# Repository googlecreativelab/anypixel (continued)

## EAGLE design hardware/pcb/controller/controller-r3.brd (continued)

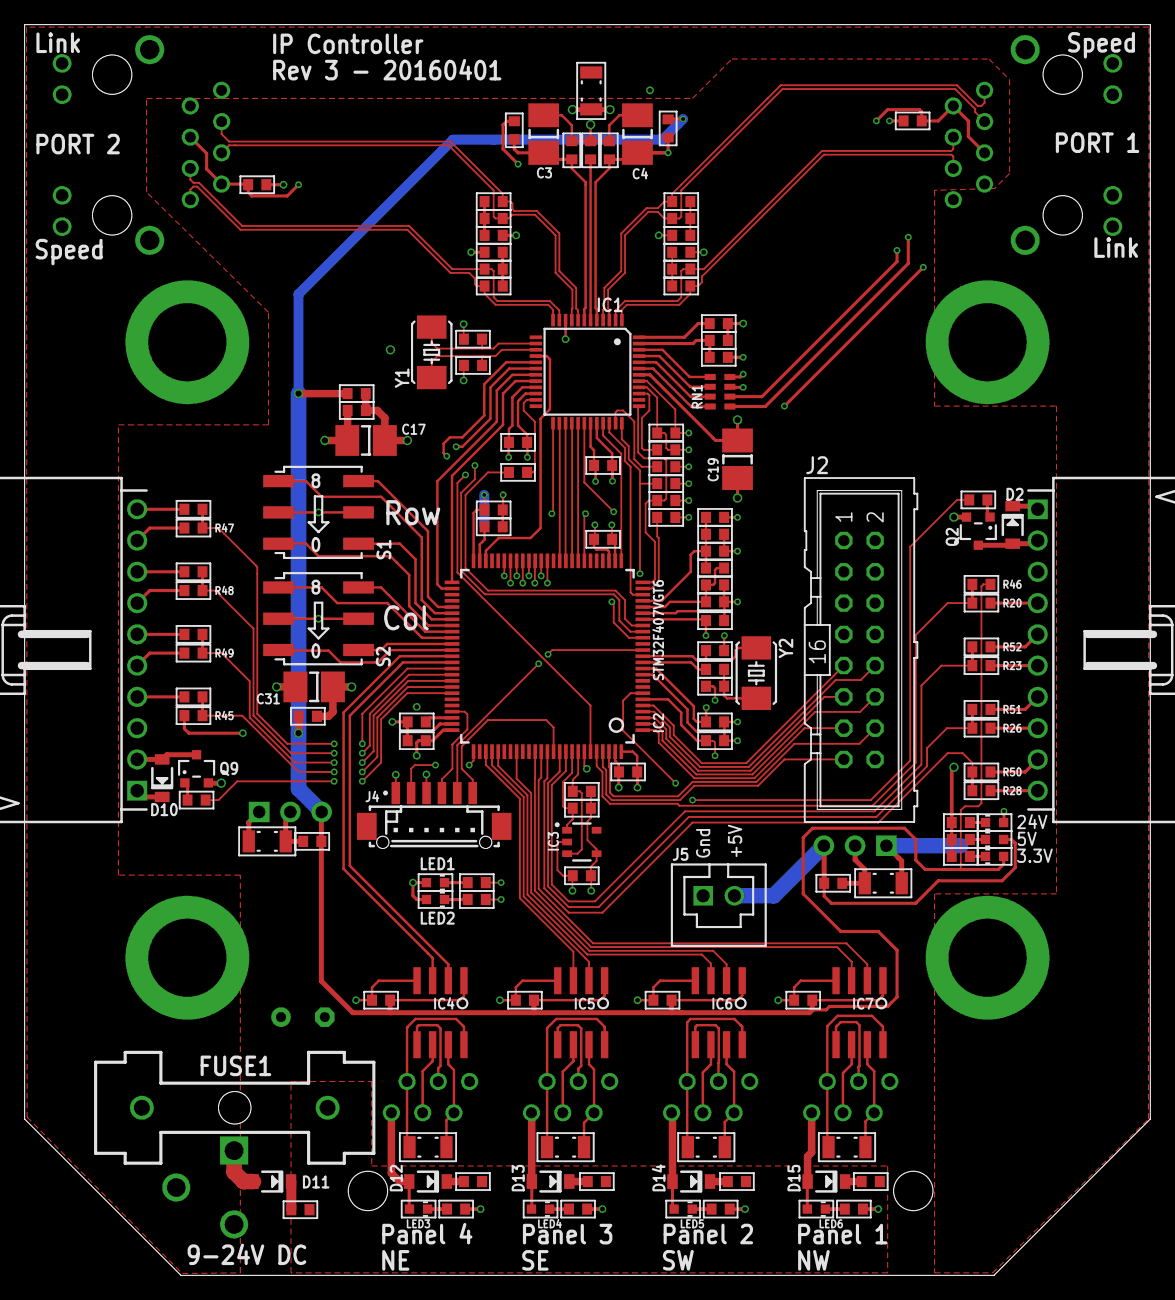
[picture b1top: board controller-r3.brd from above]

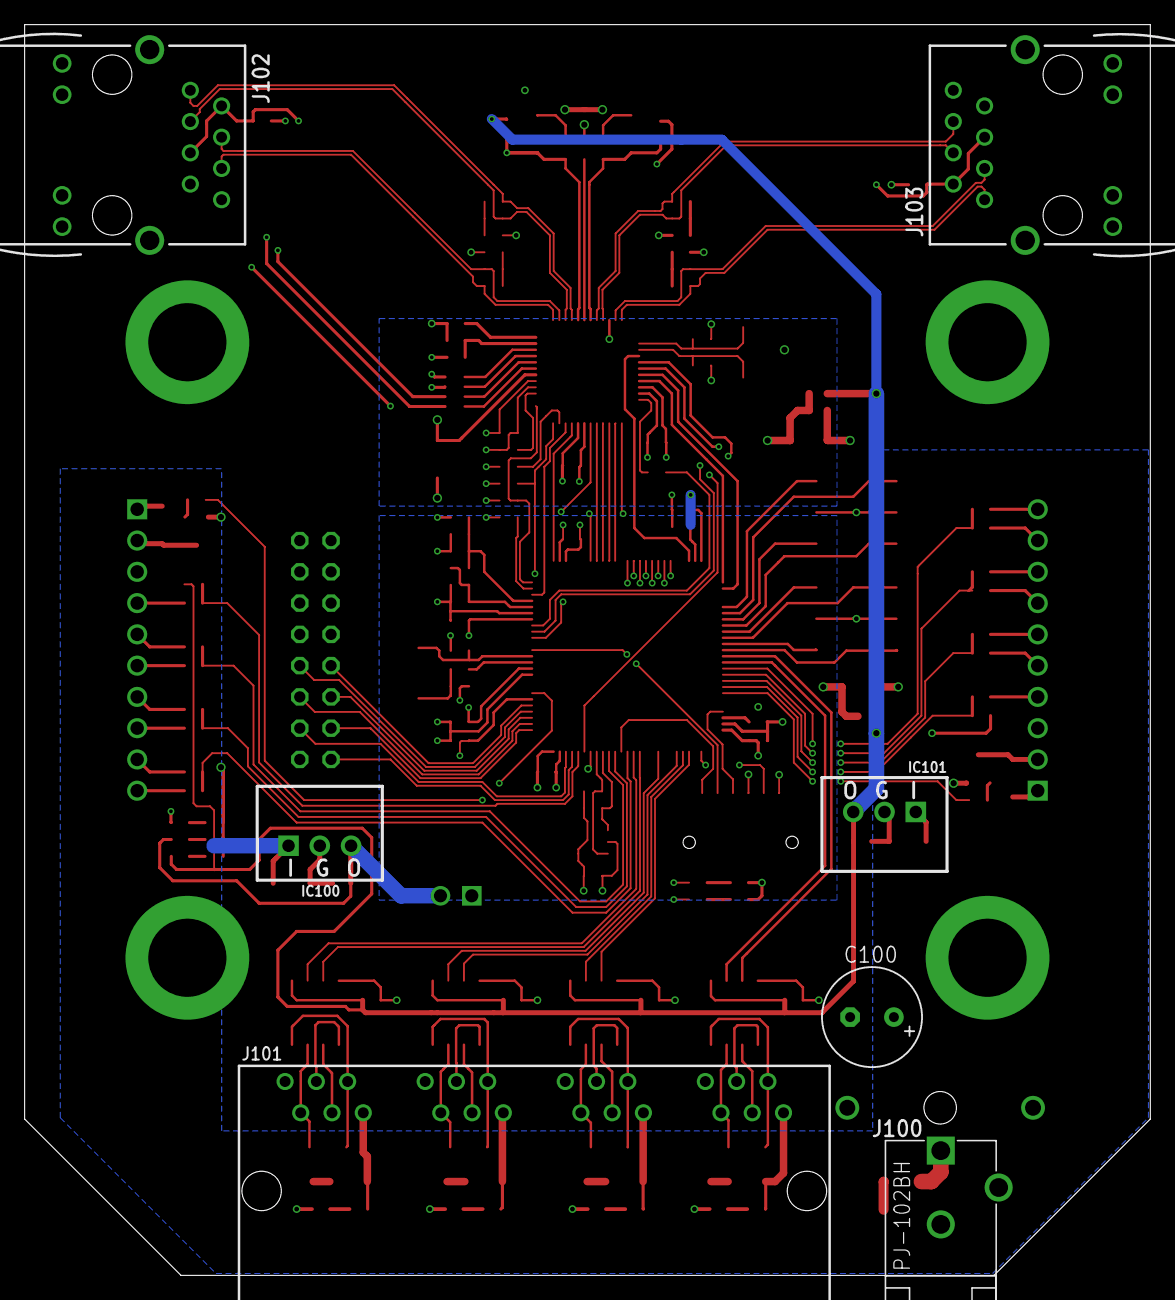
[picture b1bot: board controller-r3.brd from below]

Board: 4 copper layers, 91.4 x 101.6 mm, 154 parts (7 on the bottom side), 157 nets.

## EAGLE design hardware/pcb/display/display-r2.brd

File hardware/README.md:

## Hardware

- **/mechanical** - CAD files, engineering drawings, and assembly diagrams for the buttonwall installation in NYC.
- **/pcb** - EAGLE files and PDFs for 7x7 LED grid and network controller board.
- **/wiring** - Wiring harness and power diagrams for buttonwall installation in NYC.

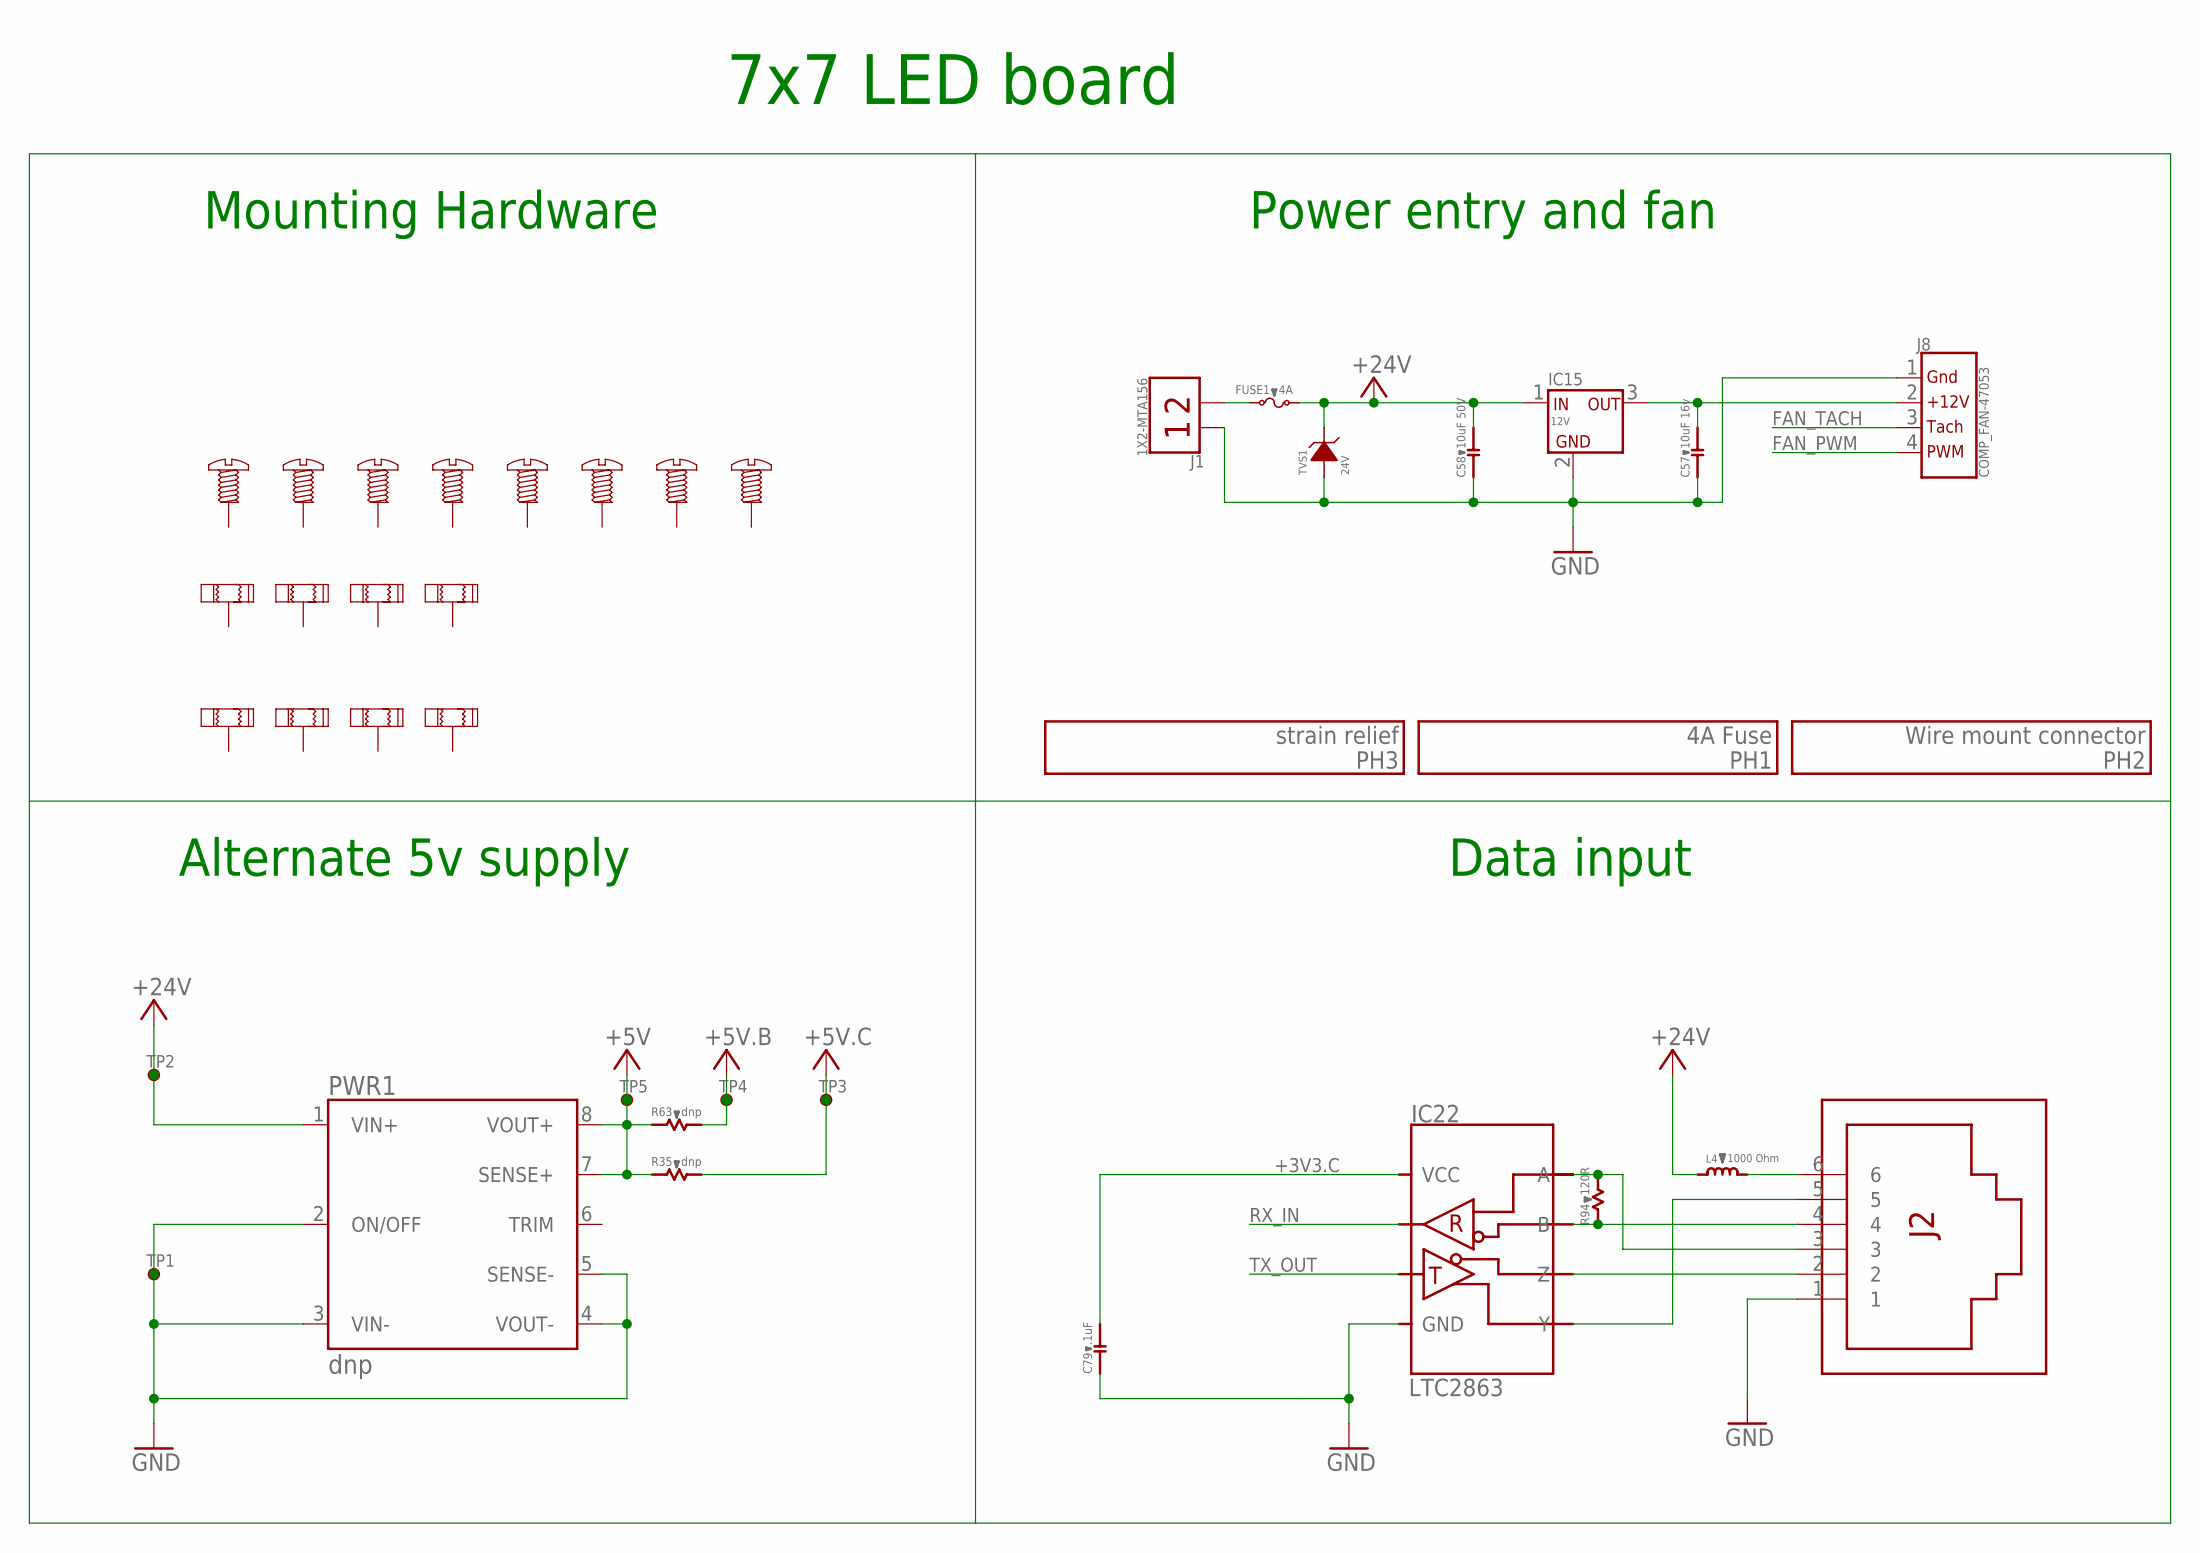
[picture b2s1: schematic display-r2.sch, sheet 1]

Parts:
C57: 10uF 16v; C0805B; PARTNO CGA4J1X5R1C106K125AC
C58: 10uF 50V; C1206B; PARTNO CL31A106KBHNNNE
C79: .1uF; C0603B; PARTNO CGA3E2X7R1H104K080AA
FUSE1: 4A; 649; PARTNO 64900001039
IC15: 12V; P7805; PARTNO P7805-Q24-S12-S
IC22: LTC2863; SO08; PARTNO LTC2863IS8-1#PBF
J1: 1X2-MTA156; 640445-2; PARTNO 640445-2
J2: RJ12-JACK-RJE01; RJE01-660-01; PARTNO RJE0166001
J8: COMP_FAN-47053; 47053; PARTNO 0470531000
L4: 1000 Ohm; R0603B; PARTNO MMZ1608R102A
NUT1, NUT2, NUT3, NUT4: NUTSMTSO-632; SMTSO-632-2ET
NUT5, NUT6, NUT7, NUT8: NUTSMTSO-832; SMTSO-832-2ET
PWR1: dnp; PWR-1/4-BRICK
R35, R63: dnp; R0805B
R94: 120R; R1206B; PARTNO CRCW1206120RFKEA
SCREW1, SCREW2, SCREW3, SCREW4, SCREW5, SCREW6, SCREW7, SCREW8: SCREW-632-0-PSHP; SMTPR-6-1
TP1, TP2, TP3, TP4, TP5: TP-CIR30; SMD_CIR30
TVS1: 24V; SMC/DO214AB; PARTNO 4.0SMDJ24A

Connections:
+3V3.C: C79.2, IC22.1 (VCC); also elsewhere on the board
+5V: PWR1.7 (SENSE+), PWR1.8 (VOUT+), R35.1, R63.1, TP5.P$1; also elsewhere on the board
+5VB: R63.2, TP4.P$1; also elsewhere on the board
+5VC: R35.2, TP3.P$1; also elsewhere on the board
+24V: C58.2, FUSE1.2, IC15.1 (IN), L4.1, PWR1.1 (VIN+), TP2.P$1, TVS1.C (CATHODE); also elsewhere on the board
+24V_OUT: J2.6, L4.2
FAN_PWM: J8.4; also elsewhere on the board
FAN_TACH: J8.3; also elsewhere on the board
GND: C57.1, C58.1, C79.1, IC15.2 (GND), IC22.4 (GND), J1.1, J2.1, J8.1, PWR1.2 (ON/OFF), PWR1.3 (VIN-), PWR1.4 (VOUT-), PWR1.5 (SENSE-), TP1.P$1, TVS1.A (ANODE); also elsewhere on the board
unnamed: FUSE1.1, J1.2
unnamed: IC22.7 (B), J2.4, R94.1
unnamed: IC22.8 (A), J2.3, R94.2
unnamed: IC22.6 (Z), J2.2
unnamed: IC22.5 (Y), J2.5
OUT: C57.2, IC15.3 (OUT), J8.2
RX_IN: IC22.2 (RO); also elsewhere on the board
TX_OUT: IC22.3 (DI); also elsewhere on the board

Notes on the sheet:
Mounting Hardware
Power entry and fan
Alternate 5v supply
Data input
7x7 LED board

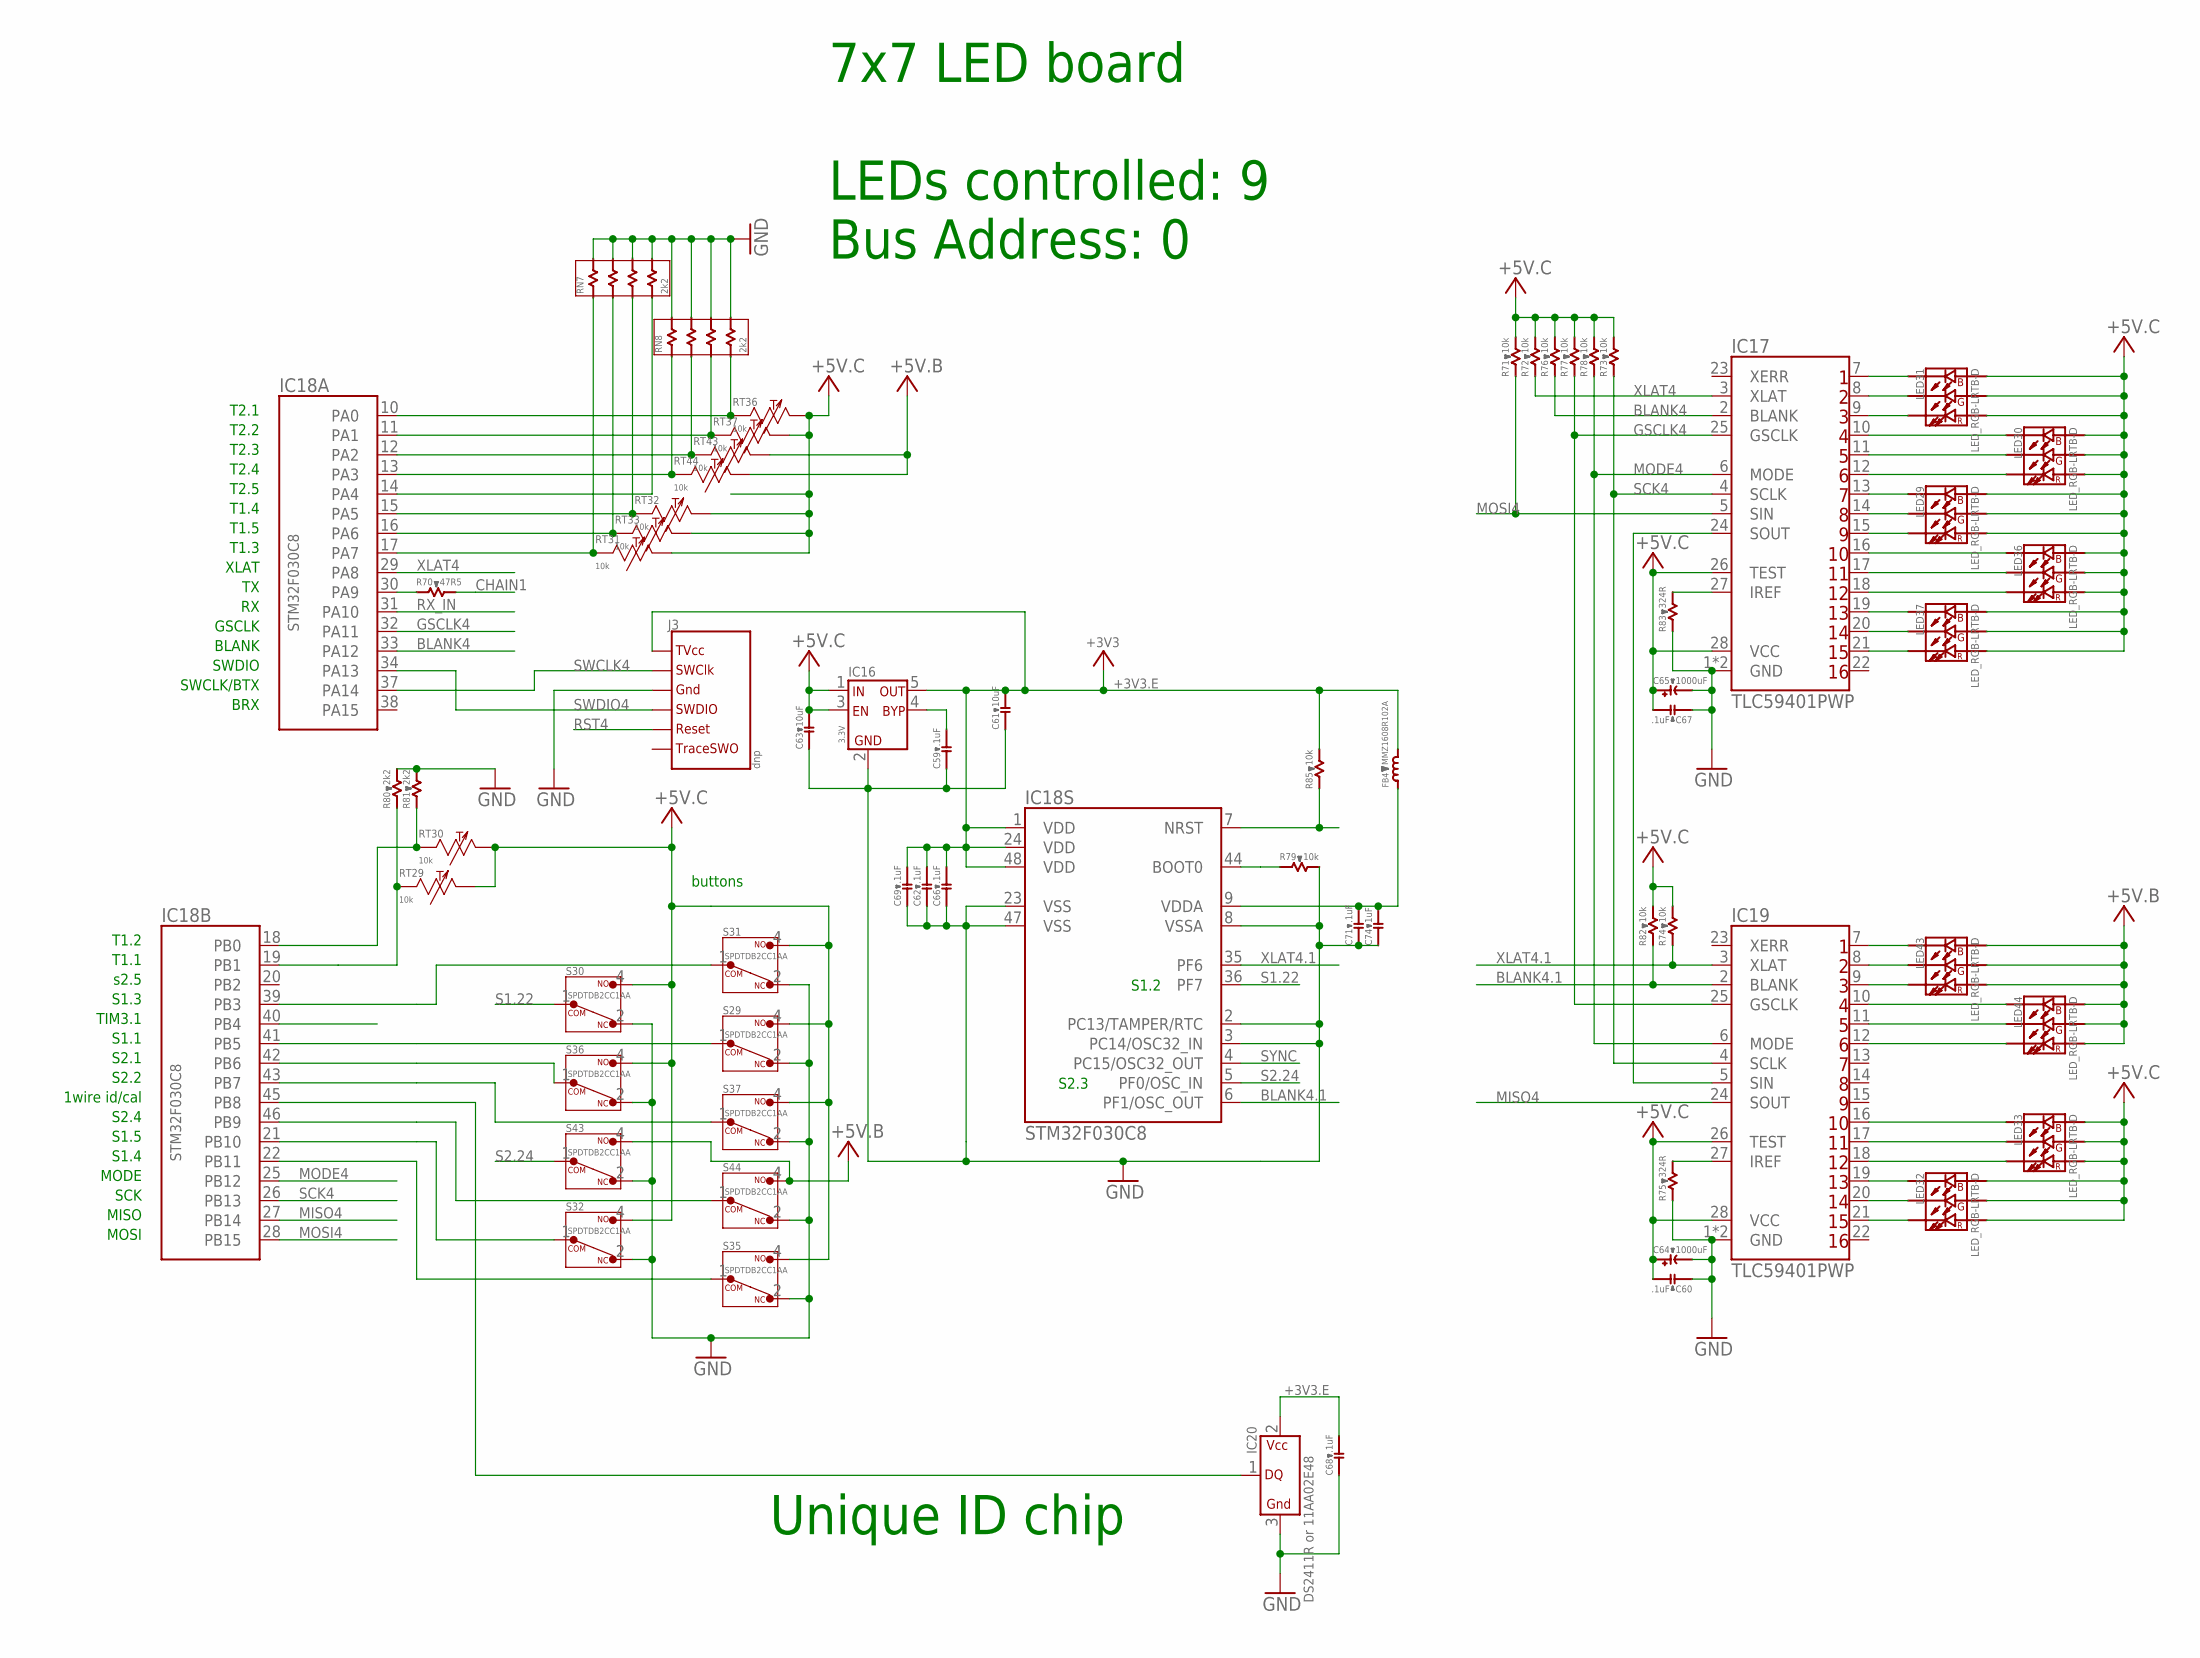
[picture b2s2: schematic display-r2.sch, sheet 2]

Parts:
C59, C60, C62, C66, C67, C68, C69, C71: .1uF; C0603B; PARTNO CGA3E2X7R1H104K080AA
C61, C63: 10uF; C0603B; PARTNO C1608X6S1A106M080AC
C64, C65: 1000uF; E5-10,5; PARTNO EKZN160ELL102MJ16S
C74: 1uF; C0603B; PARTNO CGA3E3X5R1H105K080AB
FB4: MMZ1608R102A; R0603B; PARTNO MMZ1608R102A
IC16: 3.3V; SOT-23-5; PARTNO TC2185-3.3VCTTR
IC17, IC19: TLC59401PWP; TSSOP28_PAD; PARTNO TLC59401PWPR
IC18: STM32F030C8; LQFP-48; PARTNO STM32F030C8T6
IC20: DS2411R or 11AA02E48; SOT-23; PARTNO 11AA02E48T-I/TT
J3: dnp; TC2030-IDC-NL
LED29, LED30, LED31, LED32, LED33, LED36, LED37, LED43, LED44: LED_RGB-LRTB-D; LRTB_C9TP-D; PARTNO LRTBC9TP-CWD5-1+D5E7-25+A
R70: 47R5; R0603B; PARTNO CRCW060347R5FKEA
R71, R72, R73, R74, R76, R77, R78, R79, R82, R85: 10k; R0603B; PARTNO CRCW060310K0FKEA
R75, R83: 324R; R0603B; PARTNO CRCW0603324RFKEA
R80, R81: 2k2; R0603B; PARTNO CRCW06032K20FKEA
RN7, RN8: 2k2; CAY16; PARTNO CAY16-2201F4LF
RT29, RT30, RT31, RT32, RT33, RT36, RT37, RT43, RT44: 10k; R0603Y; PARTNO NCP18XH103F03RB
S29, S30, S31, S32, S35, S36, S37, S43, S44: SPDTDB2CC1AA; DB2CC1AA; PARTNO DB2CC1AA

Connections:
+3V3.E: C61.2, C62.2, C66.2, C68.2, C69.2, FB4.2, IC16.5 (OUT), IC18.1 (VDD), IC18.24 (VDD), IC18.48 (VDD), IC20.2 (VCC), J3.1 (TVCC), R85.2
+5VB: LED43.A1 (ANODE_R), LED43.A2 (ANODE_G), LED43.A3 (ANODE_B), LED44.A1 (ANODE_R), LED44.A2 (ANODE_G), LED44.A3 (ANODE_B), RT43.2, RT44.2, S43.4 (NO), S44.4 (NO); also elsewhere on the board
+5VC: C60.2, C63.2, C64.+, C65.+, C67.2, IC16.1 (IN), IC16.3 (EN), IC17.26 (TEST), IC17.28 (VCC), IC19.26 (TEST), IC19.28 (VCC), LED29.A1 (ANODE_R), LED29.A2 (ANODE_G), LED29.A3 (ANODE_B), LED30.A1 (ANODE_R), LED30.A2 (ANODE_G), LED30.A3 (ANODE_B), LED31.A1 (ANODE_R), LED31.A2 (ANODE_G), LED31.A3 (ANODE_B), LED32.A1 (ANODE_R), LED32.A2 (ANODE_G), LED32.A3 (ANODE_B), LED33.A1 (ANODE_R), LED33.A2 (ANODE_G), LED33.A3 (ANODE_B), LED36.A1 (ANODE_R), LED36.A2 (ANODE_G), LED36.A3 (ANODE_B), LED37.A1 (ANODE_R), LED37.A2 (ANODE_G), LED37.A3 (ANODE_B), R71.2, R72.2, R73.2, R74.2, R76.2, R77.2, R78.2, R82.2, RT29.2, RT30.2, RT31.2, RT32.2, RT33.2, RT36.2, RT37.2, S29.4 (NO), S30.4 (NO), S31.4 (NO), S32.4 (NO), S35.4 (NO), S36.4 (NO), S37.4 (NO); also elsewhere on the board
BLANK4: IC17.2 (BLANK), IC18.33 (PA12), R76.1
BLANK4.1: IC18.6 (PF1/OSC_OUT), IC19.2 (BLANK), R82.1
CHAIN1: R70.2; also elsewhere on the board
GND: C59.1, C60.1, C61.1, C62.1, C63.1, C64.-, C65.-, C66.1, C67.1, C68.1, C69.1, C71.1, C74.1, IC16.2 (GND), IC17.1 (GND), IC17.PAD (GND), IC18.2 (PC13/TAMPER/RTC), IC18.3 (PC14/OSC32_IN), IC18.8 (VSSA), IC18.23 (VSS), IC18.47 (VSS), IC19.1 (GND), IC19.PAD (GND), IC20.3 (GND), J3.5 (GND), R75.1, R79.2, R80.2, R81.2, R83.1, RN7.A2, RN7.B2, RN7.C2, RN7.D2, RN8.A2, RN8.B2, RN8.C2, RN8.D2, S29.2 (NC), S30.2 (NC), S31.2 (NC), S32.2 (NC), S35.2 (NC), S36.2 (NC), S37.2 (NC), S43.2 (NC), S44.2 (NC); also elsewhere on the board
GSCLK4: IC17.25 (GSCLK), IC18.32 (PA11), IC19.25 (GSCLK), R77.1
MISO4: IC18.27 (PB14), IC19.24 (SOUT)
MODE4: IC17.6 (MODE), IC18.25 (PB12), IC19.6 (MODE), R78.1
MOSI4: IC17.5 (SIN), IC18.28 (PB15), R71.1
unnamed: IC18.44 (BOOT0), R79.1
unnamed: C71.2, C74.2, FB4.1, IC18.9 (VDDA)
unnamed: C59.2, IC16.4 (BYPASS)
unnamed: IC17.24 (SOUT), IC19.5 (SIN)
unnamed: IC19.27 (IREF), R75.2
unnamed: IC17.27 (IREF), R83.2
unnamed: IC17.7 (OUT1), LED31.C3 (CATHODE_B)
unnamed: IC17.8 (OUT2), LED31.C2 (CATHODE_G)
unnamed: IC17.9 (OUT3), LED31.C1 (CATHODE_R)
unnamed: IC17.10 (OUT4), LED30.C3 (CATHODE_B)
unnamed: IC17.11 (OUT5), LED30.C2 (CATHODE_G)
unnamed: IC17.12 (OUT6), LED30.C1 (CATHODE_R)
unnamed: IC17.13 (OUT7), LED29.C3 (CATHODE_B)
unnamed: IC17.14 (OUT8), LED29.C2 (CATHODE_G)
unnamed: IC17.15 (OUT9), LED29.C1 (CATHODE_R)
unnamed: IC17.16 (OUT10), LED36.C3 (CATHODE_B)
unnamed: IC17.17 (OUT11), LED36.C2 (CATHODE_G)
unnamed: IC17.18 (OUT12), LED36.C1 (CATHODE_R)
unnamed: IC17.19 (OUT13), LED37.C3 (CATHODE_B)
unnamed: IC17.20 (OUT14), LED37.C2 (CATHODE_G)
unnamed: IC17.21 (OUT15), LED37.C1 (CATHODE_R)
unnamed: IC19.7 (OUT1), LED43.C3 (CATHODE_B)
unnamed: IC19.8 (OUT2), LED43.C2 (CATHODE_G)
unnamed: IC19.9 (OUT3), LED43.C1 (CATHODE_R)
unnamed: IC19.10 (OUT4), LED44.C3 (CATHODE_B)
unnamed: IC19.11 (OUT5), LED44.C2 (CATHODE_G)
unnamed: IC19.12 (OUT6), LED44.C1 (CATHODE_R)
unnamed: IC19.16 (OUT10), LED33.C3 (CATHODE_B)
unnamed: IC19.17 (OUT11), LED33.C2 (CATHODE_G)
unnamed: IC19.18 (OUT12), LED33.C1 (CATHODE_R)
unnamed: IC19.19 (OUT13), LED32.C3 (CATHODE_B)
unnamed: IC19.20 (OUT14), LED32.C2 (CATHODE_G)
unnamed: IC19.21 (OUT15), LED32.C1 (CATHODE_R)
unnamed: IC18.30 (PA9), R70.1
RST4: IC18.7 (NRST), J3.3 (RESET), R85.1
RX_IN: IC18.31 (PA10); also elsewhere on the board
S1.21: IC18.39 (PB3), S31.1 (COM)
S1.22: IC18.36 (PF7), S30.1 (COM)
S1.23: IC18.41 (PB5), S29.1 (COM)
S1.24: IC18.21 (PB10), S32.1 (COM)
S1.25: IC18.22 (PB11), S35.1 (COM)
S2.22: IC18.42 (PB6), S36.1 (COM)
S2.23: IC18.43 (PB7), S37.1 (COM)
S2.24: IC18.5 (PF0/OSC_IN), S43.1 (COM)
S2.25: IC18.46 (PB9), S44.1 (COM)
SCK4: IC17.4 (SCLK), IC18.26 (PB13), IC19.4 (SCLK), R73.1
SWCLK4: IC18.37 (PA14), J3.4 (SWCLK)
SWDIO4: IC18.34 (PA13), J3.2 (SWDIO)
SYNC: IC18.4 (PC15/OSC32_OUT); also elsewhere on the board
T41: IC18.14 (PA4), RN7.D1
T42: IC18.15 (PA5), RN7.C1, RT32.1
T43: IC18.16 (PA6), RN7.B1, RT33.1
T44: IC18.17 (PA7), RN7.A1, RT31.1
T45: IC18.18 (PB0), R81.1, RT30.1
T46: IC18.19 (PB1), R80.1, RT29.1
T47: IC18.13 (PA3), RN8.A1, RT44.1
T48: IC18.12 (PA2), RN8.B1, RT43.1
T49: IC18.11 (PA1), RN8.C1, RT37.1
T50: IC18.10 (PA0), RN8.D1, RT36.1
TIM3.5: IC18.40 (PB4)
TIM16.5: IC18.45 (PB8), IC20.1 (DQ)
XLAT4: IC17.3 (XLAT), IC18.29 (PA8), R72.1
XLAT4.1: IC18.35 (PF6), IC19.3 (XLAT), R74.1

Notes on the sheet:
buttons
s2.5
S1.3
TIM3.1
S1.1
S2.1
S2.2
1wire id/cal
S2.4
S1.5
S1.4
T1.1
T1.2
MODE
SCK
MISO
MOSI
T2.1
T2.2
T2.3
T2.4
T2.5
T1.4
T1.5
T1.3
XLAT
GSCLK
BLANK
SWDIO
SWCLK/BTX
BRX
S1.2
S2.3
LEDs controlled: 9 Bus Address: 0
Unique ID chip
7x7 LED board

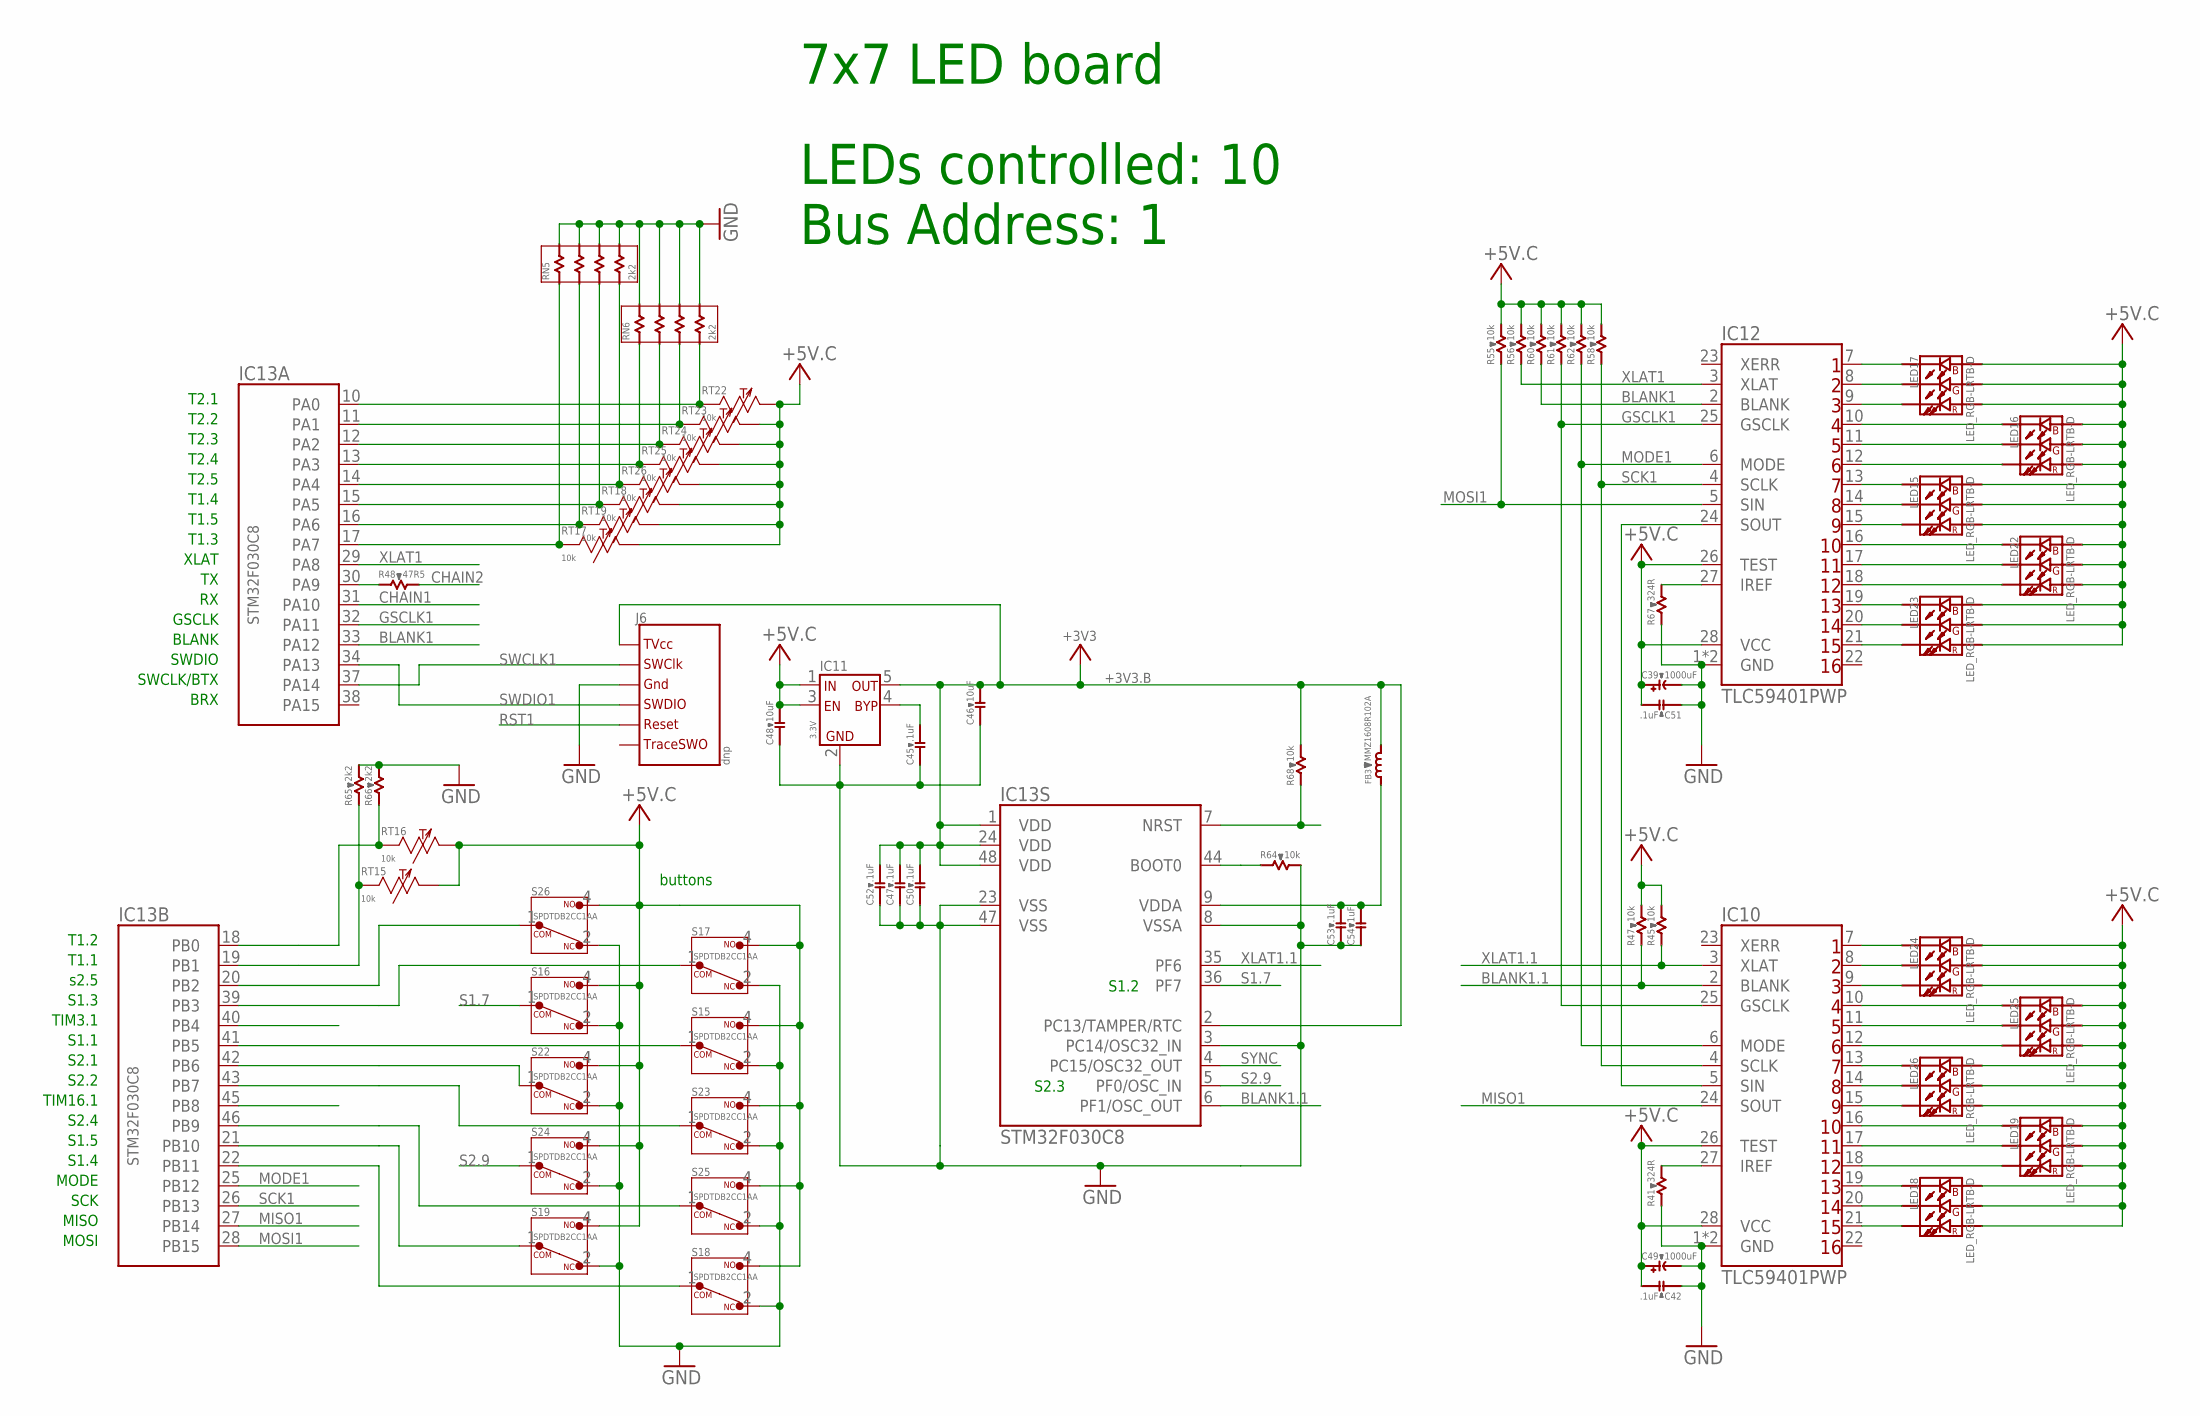
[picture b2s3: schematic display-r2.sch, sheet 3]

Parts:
C39, C49: 1000uF; E5-10,5; PARTNO EKZN160ELL102MJ16S
C42, C45, C47, C50, C51, C52, C53: .1uF; C0603B; PARTNO CGA3E2X7R1H104K080AA
C46, C48: 10uF; C0603B; PARTNO C1608X6S1A106M080AC
C54: 1uF; C0603B; PARTNO CGA3E3X5R1H105K080AB
FB3: MMZ1608R102A; R0603B; PARTNO MMZ1608R102A
IC10, IC12: TLC59401PWP; TSSOP28_PAD; PARTNO TLC59401PWPR
IC11: 3.3V; SOT-23-5; PARTNO TC2185-3.3VCTTR
IC13: STM32F030C8; LQFP-48; PARTNO STM32F030C8T6
J6: dnp; TC2030-IDC-NL
LED15, LED16, LED17, LED18, LED19, LED22, LED23, LED24, LED25, LED26: LED_RGB-LRTB-D; LRTB_C9TP-D; PARTNO LRTBC9TP-CWD5-1+D5E7-25+A
R41, R67: 324R; R0603B; PARTNO CRCW0603324RFKEA
R45, R47, R55, R56, R58, R60, R61, R62, R64, R68: 10k; R0603B; PARTNO CRCW060310K0FKEA
R48: 47R5; R0603B; PARTNO CRCW060347R5FKEA
R65, R66: 2k2; R0603B; PARTNO CRCW06032K20FKEA
RN5, RN6: 2k2; CAY16; PARTNO CAY16-2201F4LF
RT15, RT16, RT17, RT18, RT19, RT22, RT23, RT24, RT25, RT26: 10k; R0603Y; PARTNO NCP18XH103F03RB
S15, S16, S17, S18, S19, S22, S23, S24, S25, S26: SPDTDB2CC1AA; DB2CC1AA; PARTNO DB2CC1AA

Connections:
+3V3.B: C46.2, C47.2, C50.2, C52.2, FB3.2, IC11.5 (OUT), IC13.1 (VDD), IC13.2 (PC13/TAMPER/RTC), IC13.24 (VDD), IC13.48 (VDD), J6.1 (TVCC), R68.2
+5VC: C39.+, C42.2, C48.2, C49.+, C51.2, IC10.26 (TEST), IC10.28 (VCC), IC11.1 (IN), IC11.3 (EN), IC12.26 (TEST), IC12.28 (VCC), LED15.A1 (ANODE_R), LED15.A2 (ANODE_G), LED15.A3 (ANODE_B), LED16.A1 (ANODE_R), LED16.A2 (ANODE_G), LED16.A3 (ANODE_B), LED17.A1 (ANODE_R), LED17.A2 (ANODE_G), LED17.A3 (ANODE_B), LED18.A1 (ANODE_R), LED18.A2 (ANODE_G), LED18.A3 (ANODE_B), LED19.A1 (ANODE_R), LED19.A2 (ANODE_G), LED19.A3 (ANODE_B), LED22.A1 (ANODE_R), LED22.A2 (ANODE_G), LED22.A3 (ANODE_B), LED23.A1 (ANODE_R), LED23.A2 (ANODE_G), LED23.A3 (ANODE_B), LED24.A1 (ANODE_R), LED24.A2 (ANODE_G), LED24.A3 (ANODE_B), LED25.A1 (ANODE_R), LED25.A2 (ANODE_G), LED25.A3 (ANODE_B), LED26.A1 (ANODE_R), LED26.A2 (ANODE_G), LED26.A3 (ANODE_B), R45.2, R47.2, R55.2, R56.2, R58.2, R60.2, R61.2, R62.2, RT15.2, RT16.2, RT17.2, RT18.2, RT19.2, RT22.2, RT23.2, RT24.2, RT25.2, RT26.2, S15.4 (NO), S16.4 (NO), S17.4 (NO), S18.4 (NO), S19.4 (NO), S22.4 (NO), S23.4 (NO), S24.4 (NO), S25.4 (NO), S26.4 (NO); also elsewhere on the board
BLANK1: IC12.2 (BLANK), IC13.33 (PA12), R60.1
BLANK1.1: IC10.2 (BLANK), IC13.6 (PF1/OSC_OUT), R47.1
CHAIN1: IC13.31 (PA10); also elsewhere on the board
CHAIN2: R48.2; also elsewhere on the board
GND: C39.-, C42.1, C45.1, C46.1, C47.1, C48.1, C49.-, C50.1, C51.1, C52.1, C53.1, C54.1, IC10.1 (GND), IC10.PAD (GND), IC11.2 (GND), IC12.1 (GND), IC12.PAD (GND), IC13.3 (PC14/OSC32_IN), IC13.8 (VSSA), IC13.23 (VSS), IC13.47 (VSS), J6.5 (GND), R41.1, R64.2, R65.2, R66.2, R67.1, RN5.A2, RN5.B2, RN5.C2, RN5.D2, RN6.A2, RN6.B2, RN6.C2, RN6.D2, S15.2 (NC), S16.2 (NC), S17.2 (NC), S18.2 (NC), S19.2 (NC), S22.2 (NC), S23.2 (NC), S24.2 (NC), S25.2 (NC), S26.2 (NC); also elsewhere on the board
GSCLK1: IC10.25 (GSCLK), IC12.25 (GSCLK), IC13.32 (PA11), R61.1
MISO1: IC10.24 (SOUT), IC13.27 (PB14)
MODE1: IC10.6 (MODE), IC12.6 (MODE), IC13.25 (PB12), R62.1
MOSI1: IC12.5 (SIN), IC13.28 (PB15), R55.1
unnamed: IC13.44 (BOOT0), R64.1
unnamed: C53.2, C54.2, FB3.1, IC13.9 (VDDA)
unnamed: C45.2, IC11.4 (BYPASS)
unnamed: IC10.5 (SIN), IC12.24 (SOUT)
unnamed: IC10.27 (IREF), R41.2
unnamed: IC12.27 (IREF), R67.2
unnamed: IC12.7 (OUT1), LED17.C3 (CATHODE_B)
unnamed: IC12.8 (OUT2), LED17.C2 (CATHODE_G)
unnamed: IC12.9 (OUT3), LED17.C1 (CATHODE_R)
unnamed: IC12.10 (OUT4), LED16.C3 (CATHODE_B)
unnamed: IC12.11 (OUT5), LED16.C2 (CATHODE_G)
unnamed: IC12.12 (OUT6), LED16.C1 (CATHODE_R)
unnamed: IC12.13 (OUT7), LED15.C3 (CATHODE_B)
unnamed: IC12.14 (OUT8), LED15.C2 (CATHODE_G)
unnamed: IC12.15 (OUT9), LED15.C1 (CATHODE_R)
unnamed: IC12.16 (OUT10), LED22.C3 (CATHODE_B)
unnamed: IC12.17 (OUT11), LED22.C2 (CATHODE_G)
unnamed: IC12.18 (OUT12), LED22.C1 (CATHODE_R)
unnamed: IC12.19 (OUT13), LED23.C3 (CATHODE_B)
unnamed: IC12.20 (OUT14), LED23.C2 (CATHODE_G)
unnamed: IC12.21 (OUT15), LED23.C1 (CATHODE_R)
unnamed: IC10.7 (OUT1), LED24.C3 (CATHODE_B)
unnamed: IC10.8 (OUT2), LED24.C2 (CATHODE_G)
unnamed: IC10.9 (OUT3), LED24.C1 (CATHODE_R)
unnamed: IC10.10 (OUT4), LED25.C3 (CATHODE_B)
unnamed: IC10.11 (OUT5), LED25.C2 (CATHODE_G)
unnamed: IC10.12 (OUT6), LED25.C1 (CATHODE_R)
unnamed: IC10.13 (OUT7), LED26.C3 (CATHODE_B)
unnamed: IC10.14 (OUT8), LED26.C2 (CATHODE_G)
unnamed: IC10.15 (OUT9), LED26.C1 (CATHODE_R)
unnamed: IC10.16 (OUT10), LED19.C3 (CATHODE_B)
unnamed: IC10.17 (OUT11), LED19.C2 (CATHODE_G)
unnamed: IC10.18 (OUT12), LED19.C1 (CATHODE_R)
unnamed: IC10.19 (OUT13), LED18.C3 (CATHODE_B)
unnamed: IC10.20 (OUT14), LED18.C2 (CATHODE_G)
unnamed: IC10.21 (OUT15), LED18.C1 (CATHODE_R)
unnamed: IC13.30 (PA9), R48.1
RST1: IC13.7 (NRST), J6.3 (RESET), R68.1
S1.6: IC13.39 (PB3), S17.1 (COM)
S1.7: IC13.36 (PF7), S16.1 (COM)
S1.8: IC13.41 (PB5), S15.1 (COM)
S1.9: IC13.21 (PB10), S19.1 (COM)
S1.10: IC13.22 (PB11), S18.1 (COM)
S2.6: IC13.20 (PB2), S26.1 (COM)
S2.7: IC13.42 (PB6), S22.1 (COM)
S2.8: IC13.43 (PB7), S23.1 (COM)
S2.9: IC13.5 (PF0/OSC_IN), S24.1 (COM)
S2.10: IC13.46 (PB9), S25.1 (COM)
SCK1: IC10.4 (SCLK), IC12.4 (SCLK), IC13.26 (PB13), R58.1
SWCLK1: IC13.37 (PA14), J6.4 (SWCLK)
SWDIO1: IC13.34 (PA13), J6.2 (SWDIO)
SYNC: IC13.4 (PC15/OSC32_OUT); also elsewhere on the board
T11: IC13.14 (PA4), RN5.D1, RT26.1
T12: IC13.15 (PA5), RN5.C1, RT18.1
T13: IC13.16 (PA6), RN5.B1, RT19.1
T14: IC13.17 (PA7), RN5.A1, RT17.1
T15: IC13.18 (PB0), R66.1, RT16.1
T16: IC13.19 (PB1), R65.1, RT15.1
T17: IC13.13 (PA3), RN6.A1, RT25.1
T18: IC13.12 (PA2), RN6.B1, RT24.1
T19: IC13.11 (PA1), RN6.C1, RT23.1
T20: IC13.10 (PA0), RN6.D1, RT22.1
TIM3.2: IC13.40 (PB4)
TIM16.2: IC13.45 (PB8)
XLAT1: IC12.3 (XLAT), IC13.29 (PA8), R56.1
XLAT1.1: IC10.3 (XLAT), IC13.35 (PF6), R45.1

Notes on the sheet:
buttons
s2.5
S1.3
TIM3.1
S1.1
S2.1
S2.2
TIM16.1
S2.4
S1.5
S1.4
T1.1
T1.2
MODE
SCK
MISO
MOSI
T2.1
T2.2
T2.3
T2.4
T2.5
T1.4
T1.5
T1.3
XLAT
GSCLK
BLANK
SWDIO
SWCLK/BTX
BRX
S1.2
S2.3
LEDs controlled: 10 Bus Address: 1
7x7 LED board
